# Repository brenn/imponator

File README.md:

# imponator
Retro imponator NTH 1992 - reimplementation

# Revisjon log

Leaving this branch with second smd version using npns

1.2 Migrated to SMD

1.1 Swapped footprint for 2N7000 fets 
  - But mosfets wrongly biased, circuit buggy

1.0  PTH version 
  - LEDs are of varying intensity/quality

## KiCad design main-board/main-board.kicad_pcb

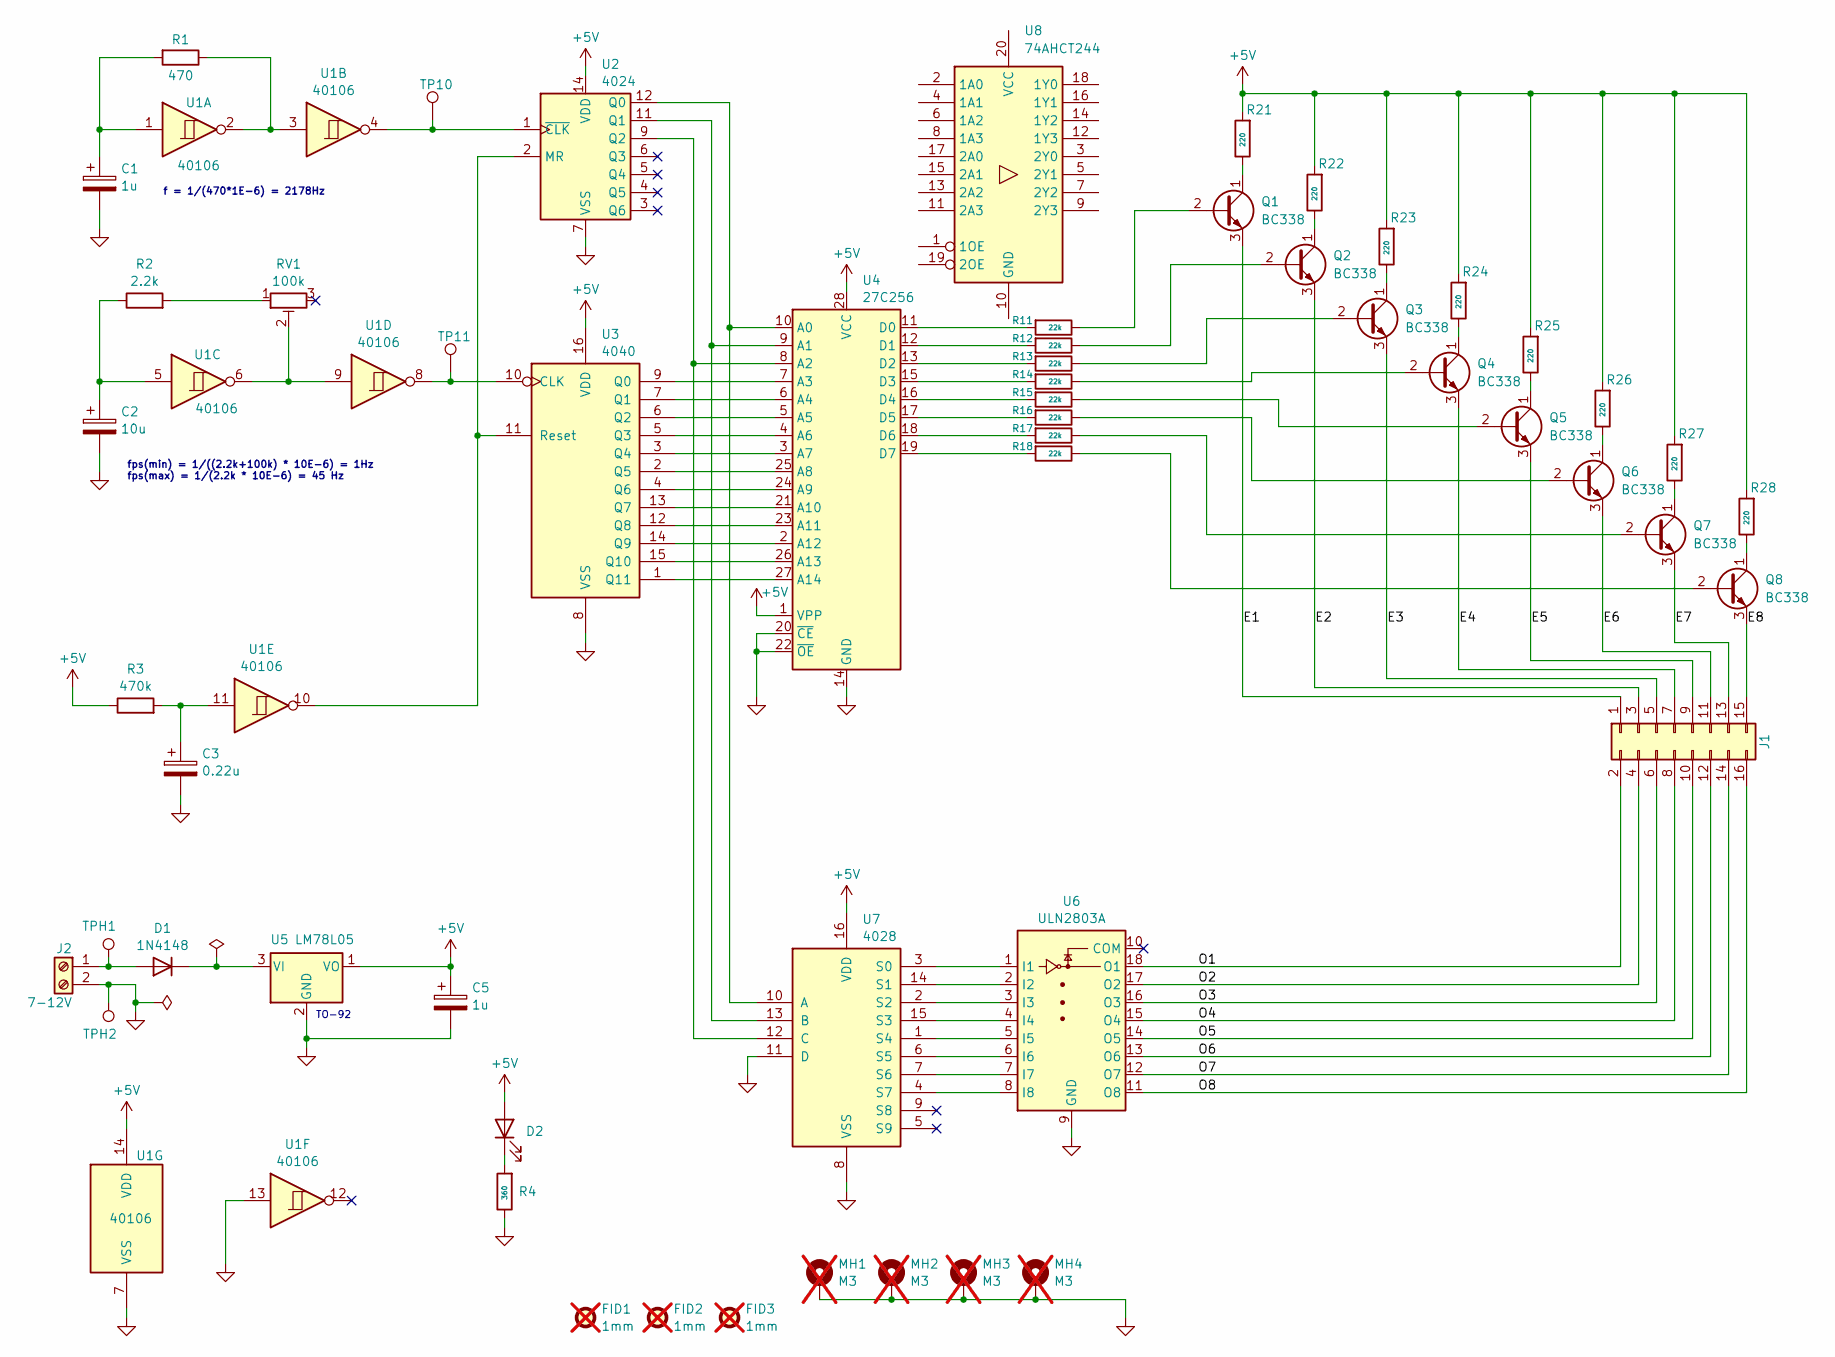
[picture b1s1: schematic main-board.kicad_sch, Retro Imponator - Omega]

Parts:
C1, C5: 1u; CP_Radial_D4.0mm_P1.50mm
C2: 10u; CP_Radial_D4.0mm_P1.50mm
C3: 0.22u; CP_Radial_D4.0mm_P1.50mm
D1: 1N4148; D_DO-35_SOD27_P7.62mm_Horizontal
D2: LED; LED_D3.0mm
FID1, FID2, FID3: 1mm; Fiducial_1mm_Mask2mm; not fitted
J1: Conn_02x08_Odd_Even; PinHeader_2x08_P2.54mm_Horizontal
J2: 7-12V; Battery_Terminals
MH1, MH2, MH3, MH4: M3; MountingHole_2.2mm_M2_DIN965_Pad; not fitted
Q1, Q2, Q3, Q4, Q5, Q6, Q7, Q8: BC338; TO-92_Inline
R1: 470; R_Axial_DIN0207_L6.3mm_D2.5mm_P10.16mm_Horizontal
R2: 2.2k; R_Axial_DIN0207_L6.3mm_D2.5mm_P10.16mm_Horizontal
R3: 470k; R_Axial_DIN0207_L6.3mm_D2.5mm_P10.16mm_Horizontal
R4: 360; R_Axial_DIN0207_L6.3mm_D2.5mm_P10.16mm_Horizontal
R11, R12, R13, R14, R15, R16, R17, R18: 22k; R_Axial_DIN0207_L6.3mm_D2.5mm_P10.16mm_Horizontal
R21, R22, R23, R24, R25, R26, R27, R28: 220; R_Axial_DIN0207_L6.3mm_D2.5mm_P10.16mm_Horizontal
RV1: 100k; Potentiometer_Wheel_3pin_Pitch4mm
TP10, TP11: TestPoint; TestPoint_Pad_D1.0mm
TPH1, TPH2: TestPoint_Hook
U1: 40106; DIP-14_W7.62mm
U2: 4024; DIP-14_W7.62mm
U3: 4040; DIP-16_W7.62mm
U4: 27C256; DIP-28_W15.24mm
U5: LM78L05; TO-92_Inline
U6: ULN2803A; DIP-18_W7.62mm
U7: 4028; DIP-16_W7.62mm
U8: 74AHCT244

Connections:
+5V: C5.1, D2.2 (A), R3.1, R21.2, R22.2, R23.2, R24.2, R25.2, R26.2, R27.2, R28.2, U1.14 (VDD), U2.14 (VDD), U3.16 (VDD), U4.1 (VPP), U4.28 (VCC), U5.1 (VO), U7.16 (VDD)
/E1: J1.1, Q1.3 (E)
/E2: J1.3, Q2.3 (E)
/E3: J1.5, Q3.3 (E)
/E4: J1.7, Q4.3 (E)
/E5: J1.9, Q5.3 (E)
/E6: J1.11, Q6.3 (E)
/E7: J1.13, Q7.3 (E)
/E8: J1.15, Q8.3 (E)
/O1: J1.2, U6.18 (O1)
/O2: J1.4, U6.17 (O2)
/O3: J1.6, U6.16 (O3)
/O4: J1.8, U6.15 (O4)
/O5: J1.10, U6.14 (O5)
/O6: J1.12, U6.13 (O6)
/O7: J1.14, U6.12 (O7)
/O8: J1.16, U6.11 (O8)
GND: C1.2, C2.2, C3.2, C5.2, J2.2, MH1.1 (1_1), MH2.1 (1_1), MH3.1 (1_1), MH4.1 (1_1), R4.1, TPH2.1 (1_1), U1.7 (VSS), U1.13, U2.7 (VSS), U3.8 (VSS), U4.14 (GND), U4.20 (~CE), U4.22 (~OE), U5.2 (GND), U6.9 (GND), U7.8 (VSS), U7.11 (D)
unnamed: C1.1, R1.2, U1.1
unnamed: C2.1, R2.1, U1.5
unnamed: C3.1, R3.2, U1.11
unnamed: D1.2 (A), J2.1, TPH1.1 (1_1)
unnamed: D1.1 (K), U5.3 (VI)
unnamed: D2.1 (K), R4.2
unnamed: Q1.2 (B), R11.1
unnamed: Q1.1 (C), R21.1
unnamed: Q2.2 (B), R12.1
unnamed: Q2.1 (C), R22.1
unnamed: Q3.2 (B), R13.1
unnamed: Q3.1 (C), R23.1
unnamed: Q4.2 (B), R14.1
unnamed: Q4.1 (C), R24.1
unnamed: Q5.2 (B), R15.1
unnamed: Q5.1 (C), R25.1
unnamed: Q6.2 (B), R16.1
unnamed: Q6.1 (C), R26.1
unnamed: Q7.2 (B), R17.1
unnamed: Q7.1 (C), R27.1
unnamed: Q8.2 (B), R18.1
unnamed: Q8.1 (C), R28.1
unnamed: R1.1, U1.2, U1.3
unnamed: R2.2, RV1.1
unnamed: RV1.2, U1.6, U1.9
unnamed: U1.10, U2.2 (MR), U3.11 (Reset)
unnamed: U2.12 (Q0), U4.10 (A0), U7.10 (A)
unnamed: U2.11 (Q1), U4.9 (A1), U7.13 (B)
unnamed: U2.9 (Q2), U4.8 (A2), U7.12 (C)
unnamed: TP10.1 (1_1), U1.4, U2.1 (~CLK)
unnamed: TP11.1 (1_1), U1.8, U3.10 (CLK)
unnamed: U3.9 (Q0), U4.7 (A3)
unnamed: U3.7 (Q1), U4.6 (A4)
unnamed: U3.6 (Q2), U4.5 (A5)
unnamed: U3.5 (Q3), U4.4 (A6)
unnamed: U3.3 (Q4), U4.3 (A7)
unnamed: U3.2 (Q5), U4.25 (A8)
unnamed: U3.4 (Q6), U4.24 (A9)
unnamed: U3.13 (Q7), U4.21 (A10)
unnamed: U3.12 (Q8), U4.23 (A11)
unnamed: U3.14 (Q9), U4.2 (A12)
unnamed: U3.15 (Q10), U4.26 (A13)
unnamed: U3.1 (Q11), U4.27 (A14)
unnamed: R11.2, U4.11 (D0)
unnamed: R12.2, U4.12 (D1)
unnamed: R13.2, U4.13 (D2)
unnamed: R14.2, U4.15 (D3)
unnamed: R15.2, U4.16 (D4)
unnamed: R16.2, U4.17 (D5)
unnamed: R17.2, U4.18 (D6)
unnamed: R18.2, U4.19 (D7)
unnamed: U6.1 (I1), U7.3 (S0)
unnamed: U6.2 (I2), U7.14 (S1)
unnamed: U6.3 (I3), U7.2 (S2)
unnamed: U6.4 (I4), U7.15 (S3)
unnamed: U6.5 (I5), U7.1 (S4)
unnamed: U6.6 (I6), U7.6 (S5)
unnamed: U6.7 (I7), U7.7 (S6)
unnamed: U6.8 (I8), U7.4 (S7)

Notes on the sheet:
fps(min) = 1/((2.2k+100k) * 10E-6) = 1Hz fps(max) = 1/(2.2k * 10E-6) = 45 Hz
TO-92
f = 1/(470*1E-6) = 2178Hz

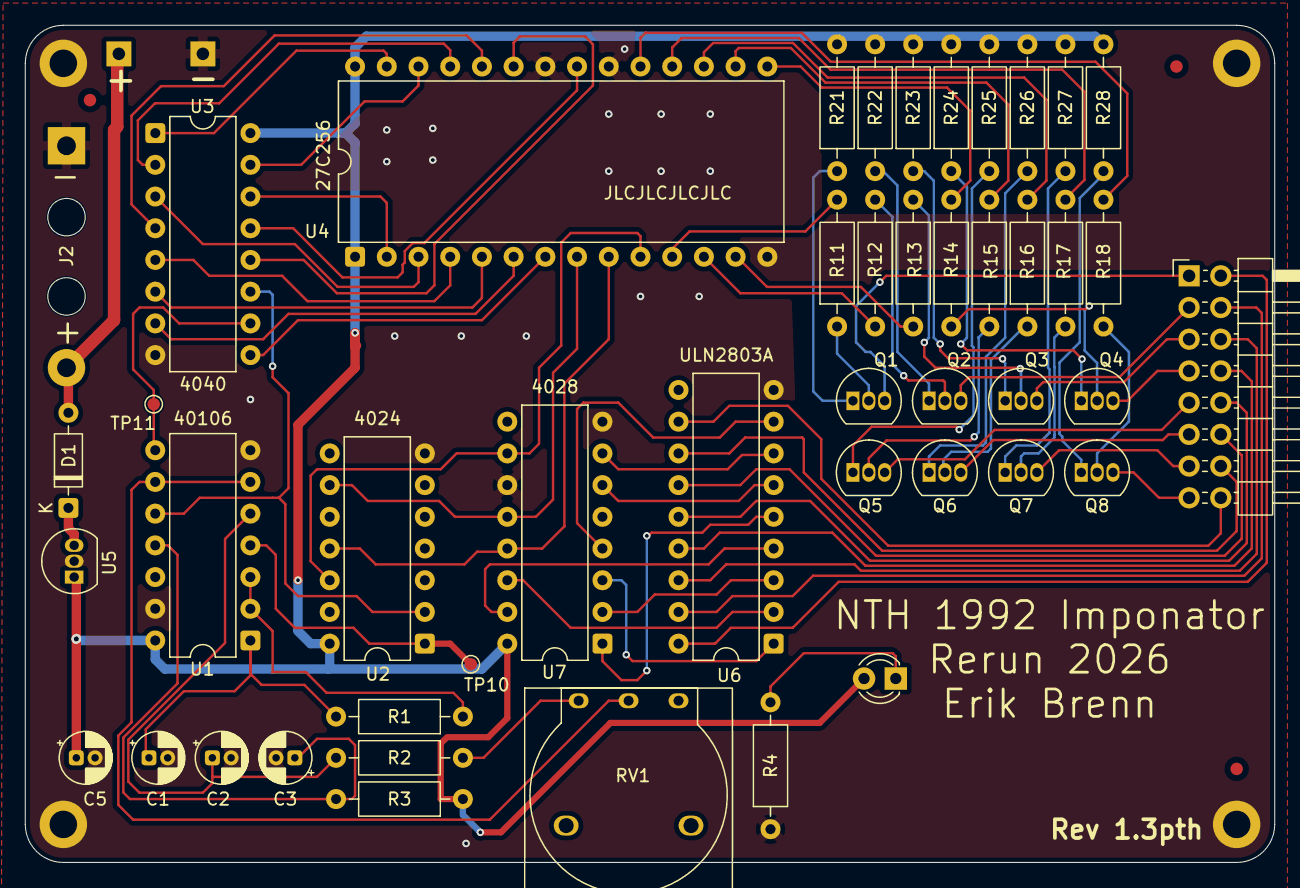
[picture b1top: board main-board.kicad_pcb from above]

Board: 2 copper layers, 100.1 x 67.1 mm, 55 parts (0 on the bottom side), 77 nets.

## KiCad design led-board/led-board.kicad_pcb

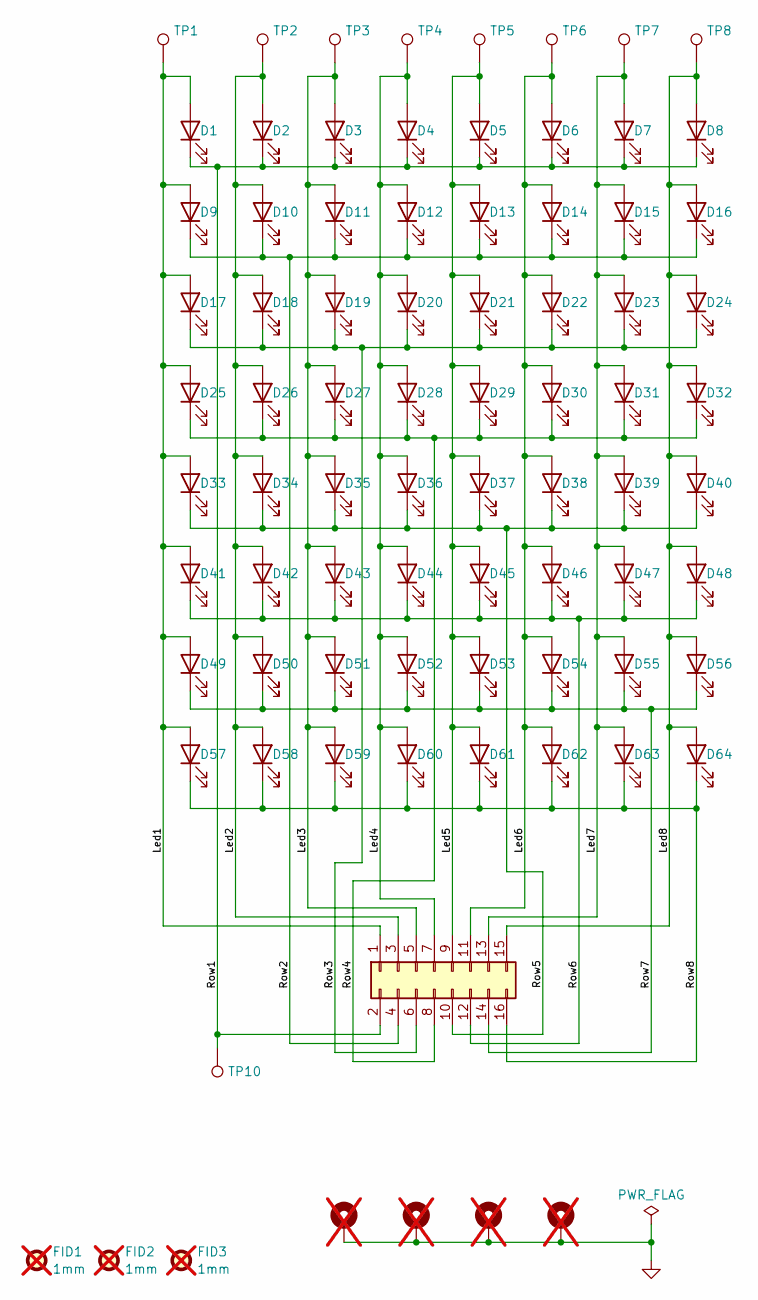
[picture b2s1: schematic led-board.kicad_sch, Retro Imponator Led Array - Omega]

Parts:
D1, D2, D3, D4, D5, D6, D7, D8, D9, D10, D11, D12, D13, D14, D15, D16, D17, D18, D19, D20, D21, D22, D23, D24, D25, D26, D27, D28, D29, D30, D31, D32, D33, D34, D35, D36, D37, D38, D39, D40, D41, D42, D43, D44, D45, D46, D47, D48, D49, D50, D51, D52, D53, D54, D55, D56, D57, D58, D59, D60, D61, D62, D63, D64: LED; LED_D3.0mm
FID1, FID2, FID3: 1mm; Fiducial_1mm_Mask2mm; not fitted
J1: Conn_02x08_Odd_Even; PinHeader_2x08_P2.54mm_Horizontal
MH1, MH2, MH3, MH4: M3; MountingHole_2.2mm_M2_DIN965_Pad; not fitted
TP1, TP2, TP3, TP4, TP5, TP6, TP7, TP8, TP10: TestPoint; TestPoint_Pad_D1.0mm

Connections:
/Led1: D1.2 (A), D9.2 (A), D17.2 (A), D25.2 (A), D33.2 (A), D41.2 (A), D49.2 (A), D57.2 (A), J1.1, TP1.1 (1_1)
/Led2: D2.2 (A), D10.2 (A), D18.2 (A), D26.2 (A), D34.2 (A), D42.2 (A), D50.2 (A), D58.2 (A), J1.3, TP2.1 (1_1)
/Led3: D3.2 (A), D11.2 (A), D19.2 (A), D27.2 (A), D35.2 (A), D43.2 (A), D51.2 (A), D59.2 (A), J1.5, TP3.1 (1_1)
/Led4: D4.2 (A), D12.2 (A), D20.2 (A), D28.2 (A), D36.2 (A), D44.2 (A), D52.2 (A), D60.2 (A), J1.7, TP4.1 (1_1)
/Led5: D5.2 (A), D13.2 (A), D21.2 (A), D29.2 (A), D37.2 (A), D45.2 (A), D53.2 (A), D61.2 (A), J1.9, TP5.1 (1_1)
/Led6: D6.2 (A), D14.2 (A), D22.2 (A), D30.2 (A), D38.2 (A), D46.2 (A), D54.2 (A), D62.2 (A), J1.11, TP6.1 (1_1)
/Led7: D7.2 (A), D15.2 (A), D23.2 (A), D31.2 (A), D39.2 (A), D47.2 (A), D55.2 (A), D63.2 (A), J1.13, TP7.1 (1_1)
/Led8: D8.2 (A), D16.2 (A), D24.2 (A), D32.2 (A), D40.2 (A), D48.2 (A), D56.2 (A), D64.2 (A), J1.15, TP8.1 (1_1)
/Row1: D1.1 (K), D2.1 (K), D3.1 (K), D4.1 (K), D5.1 (K), D6.1 (K), D7.1 (K), D8.1 (K), J1.2, TP10.1 (1_1)
/Row2: D9.1 (K), D10.1 (K), D11.1 (K), D12.1 (K), D13.1 (K), D14.1 (K), D15.1 (K), D16.1 (K), J1.4
/Row3: D17.1 (K), D18.1 (K), D19.1 (K), D20.1 (K), D21.1 (K), D22.1 (K), D23.1 (K), D24.1 (K), J1.6
/Row4: D25.1 (K), D26.1 (K), D27.1 (K), D28.1 (K), D29.1 (K), D30.1 (K), D31.1 (K), D32.1 (K), J1.8
/Row5: D33.1 (K), D34.1 (K), D35.1 (K), D36.1 (K), D37.1 (K), D38.1 (K), D39.1 (K), D40.1 (K), J1.10
/Row6: D41.1 (K), D42.1 (K), D43.1 (K), D44.1 (K), D45.1 (K), D46.1 (K), D47.1 (K), D48.1 (K), J1.12
/Row7: D49.1 (K), D50.1 (K), D51.1 (K), D52.1 (K), D53.1 (K), D54.1 (K), D55.1 (K), D56.1 (K), J1.14
/Row8: D57.1 (K), D58.1 (K), D59.1 (K), D60.1 (K), D61.1 (K), D62.1 (K), D63.1 (K), D64.1 (K), J1.16
GND: MH1.1 (1_1), MH2.1 (1_1), MH3.1 (1_1), MH4.1 (1_1)

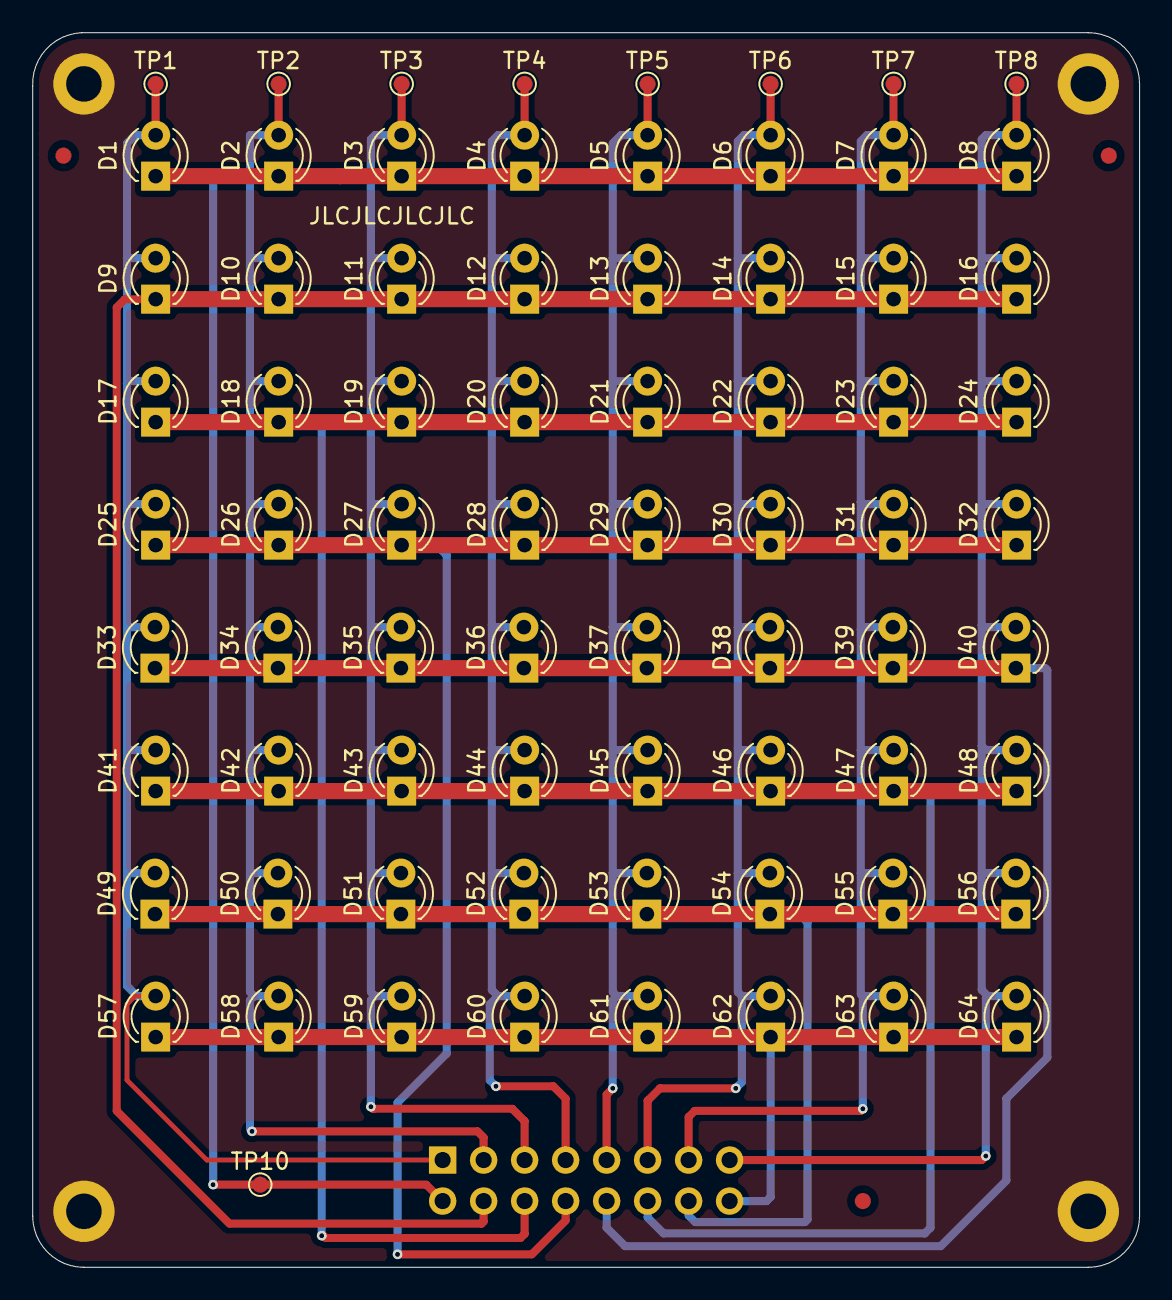
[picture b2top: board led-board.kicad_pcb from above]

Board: 2 copper layers, 68.6 x 76.5 mm, 81 parts (1 on the bottom side), 17 nets.

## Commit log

2026-02-28 Initial checking
2026-02-28 reorg
2026-02-28 layout done
2026-03-01 Finalized Rev-1.0
2026-03-14 Enlarged legs on pot-meter footprint
2026-03-15 fixed 2n7000 footprint and added testpoints
2026-03-16 started smd conversion
2026-03-16 docs
2026-03-17 completed routing of smd board
2026-04-06 n-channel high side switching doesn't work - morongit add .
2026-05-02 Started migrating to SMD
2026-05-02 routing complete - ready for QA
2026-05-06 new biasing and fixed footprints, shrinked pcb
2026-05-06 made biasing subcircuit for spreadsheet
2026-05-06 cleanup
2026-05-06 minor changes on pcb
2026-05-08 dummy commit - leaving this branch
2026-05-09 footprint fixes etc
2026-05-09 pth layout in progress
2026-05-09 led-board minor update
2026-05-09 completed pth layout for production
2026-05-09 gitignore for production files
2026-05-09 sat version to 1.3pre on pcb
2026-05-09 gitignore update
